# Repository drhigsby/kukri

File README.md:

# kukri
 Kukri is a PM-based WKL unibody split van-like with a dedicated arrow cluster.

Required Hardware:

-switches

-diodes (smd or tht)

-PM or equivalent

-keycaps

-up to 2x roller encoders part#EVQWGD001
https://www.aliexpress.com/item/4001293888953.html?spm=a2g0s.9042311.0.0.4e014c4dfA4Ye7

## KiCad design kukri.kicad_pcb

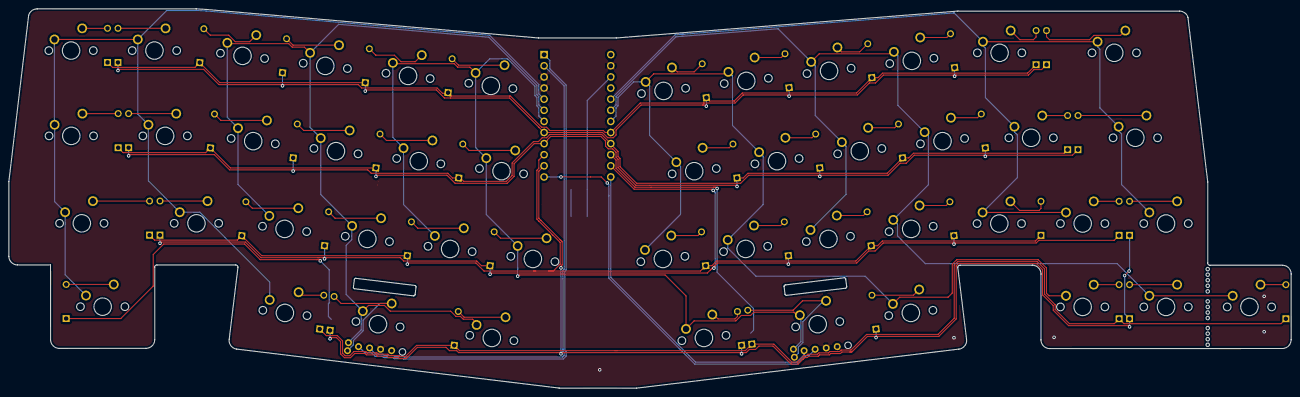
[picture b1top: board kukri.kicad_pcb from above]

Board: 2 copper layers, 293.0 x 86.7 mm, 98 parts (1 on the bottom side), 67 nets.

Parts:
D1, D2, D3, D4, D5, D6, D7, D8, D9, D10, D11, D12, D13, D14, D15, D16, D17, D18, D19, D20, D21, D22, D23, D24, D25, D26, D27, D28, D29, D30, D31, D32, D33, D34, D35, D36, D37, D38, D39, D40, D41, D42, D43, D44, D45, D46, D47: D_Small; Diode-Hybrid-Back
MX1, MX2, MX3, MX4, MX5, MX6, MX7, MX8, MX9, MX10, MX11, MX14, MX15, MX16, MX17, MX18, MX19, MX20, MX21, MX22, MX23, MX26, MX27, MX28, MX29, MX30, MX31, MX32, MX33, MX34, MX35, MX36, MX39, MX42, MX44, MX45, MX46, MX47: MX-NoLED; MXOnly-1U-NoLED
MX12, MX25, MX40-1.75u1, MX41-1.75u1: MX-NoLED; MXOnly-1.75U-NoLED
MX13, MX37, MX38, MX43: MX-NoLED; MXOnly-1.25U-NoLED
MX24: MX-NoLED; MXOnly-1.5U-NoLED
RE1, RE2: Rotary_Encoder_Switch; RollerEncoder_Panasonic_EVQWGD001
SW1: SW_Push; SW_SPST_SKQG_WithStem
U1: ProMicro; ArduinoProMicro

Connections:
39-1: MX3.1, MX4.1, MX15.1, MX16.1, MX27.1, MX28.1, MX39.1, MX40-1.75u1.1, RE1.S2, U1.6
39-2: D39.2, MX39.2, RE1.S1
42-1: MX5.1, MX6.1, MX17.1, MX18.1, MX29.1, MX30.1, MX41-1.75u1.1, MX42.1, RE2.S2, U1.7
42-2: D42.2, MX42.2, RE2.S1
GND: RE1.C, RE2.C, SW1.1, U1.3, U1.4, U1.23
unnamed: D1.2, MX1.2
unnamed: D2.2, MX2.2
unnamed: D3.2, MX3.2
unnamed: D4.2, MX4.2
unnamed: D5.2, MX5.2
unnamed: D6.2, MX6.2
unnamed: D7.2, MX7.2
unnamed: D8.2, MX8.2
unnamed: D9.2, MX9.2
unnamed: D10.2, MX10.2
unnamed: D11.2, MX11.2
unnamed: D12.2, MX12.2
unnamed: D13.2, MX13.2
unnamed: D14.2, MX14.2
unnamed: D15.2, MX15.2
unnamed: D16.2, MX16.2
unnamed: D17.2, MX17.2
unnamed: D18.2, MX18.2
unnamed: D19.2, MX19.2
unnamed: D20.2, MX20.2
unnamed: D21.2, MX21.2
unnamed: D22.2, MX22.2
unnamed: D23.2, MX23.2
unnamed: D24.2, MX24.2
unnamed: D25.2, MX25.2
unnamed: D26.2, MX26.2
unnamed: D27.2, MX27.2
unnamed: D28.2, MX28.2
unnamed: D29.2, MX29.2
unnamed: D30.2, MX30.2
unnamed: D31.2, MX31.2
unnamed: D32.2, MX32.2
unnamed: D33.2, MX33.2
unnamed: D34.2, MX34.2
unnamed: D35.2, MX35.2
unnamed: D36.2, MX36.2
unnamed: D37.2, MX37.2
unnamed: D38.2, MX38.2
unnamed: D40.2, MX40-1.75u1.2
unnamed: D41.2, MX41-1.75u1.2
unnamed: D43.2, MX43.2
unnamed: D44.2, MX44.2
unnamed: D45.2, MX45.2
unnamed: D46.2, MX46.2
unnamed: D47.2, MX47.2
PMA: RE2.A, U1.13
PMB: RE2.B, U1.12
PMC: RE1.A, U1.1
PMD: RE1.B, U1.2
RST: SW1.2, U1.22
c1: D1.1, D3.1, D5.1, D7.1, D9.1, D11.1, U1.8
c2: D2.1, D4.1, D6.1, D8.1, D10.1, D12.1, U1.17
c3: D13.1, D15.1, D17.1, D19.1, D21.1, D23.1, U1.9
c4: D14.1, D16.1, D18.1, D20.1, D22.1, D24.1, U1.16
c5: D25.1, D27.1, D29.1, D31.1, D33.1, D35.1, U1.10
c6: D26.1, D28.1, D30.1, D32.1, D34.1, D36.1, U1.14
c7: D37.1, D39.1, D41.1, D43.1, D45.1, D47.1, U1.11
c8: D38.1, D40.1, D42.1, D44.1, D46.1, U1.15
r1: MX1.1, MX2.1, MX13.1, MX14.1, MX25.1, MX26.1, MX37.1, MX38.1, U1.5
r4: MX7.1, MX8.1, MX19.1, MX20.1, MX31.1, MX32.1, MX43.1, MX44.1, U1.18
r5: MX9.1, MX10.1, MX21.1, MX22.1, MX33.1, MX34.1, MX45.1, MX46.1, U1.19
r6: MX11.1, MX12.1, MX23.1, MX24.1, MX35.1, MX36.1, MX47.1, U1.20

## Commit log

2021-10-28 readme update
2022-11-06 added qmk support
